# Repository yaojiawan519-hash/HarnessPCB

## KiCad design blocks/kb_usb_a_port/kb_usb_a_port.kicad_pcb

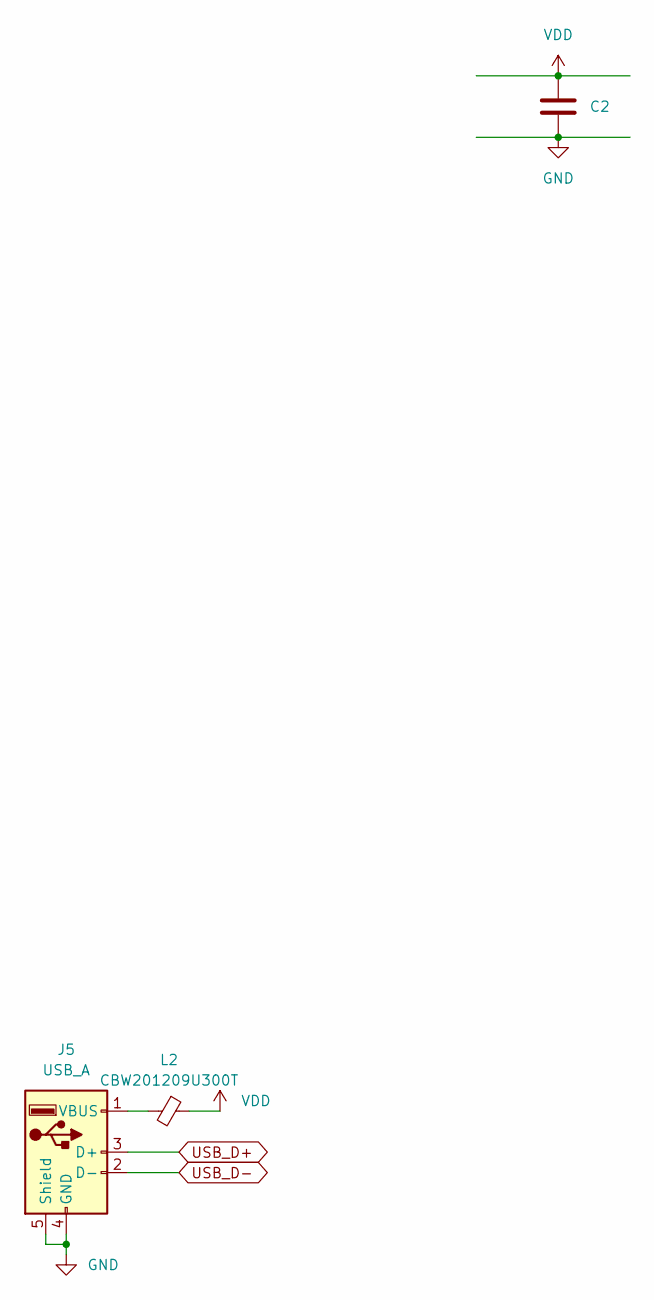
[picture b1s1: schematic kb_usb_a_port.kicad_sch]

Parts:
C2: 47uF/CL21A226MAYNNNE; C_0805_2012Metric
J5: USB_A; USB_A_CONNFLY_DS1095-WNR0
L2: CBW201209U300T; L_0805_2012Metric

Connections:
GND: C2.2, J5.4 (GND), J5.5 (Shield)
unnamed: J5.1 (VBUS), L2.2
USB_D+: J5.3 (D+)
USB_D-: J5.2 (D-)
VDD: C2.1, L2.1

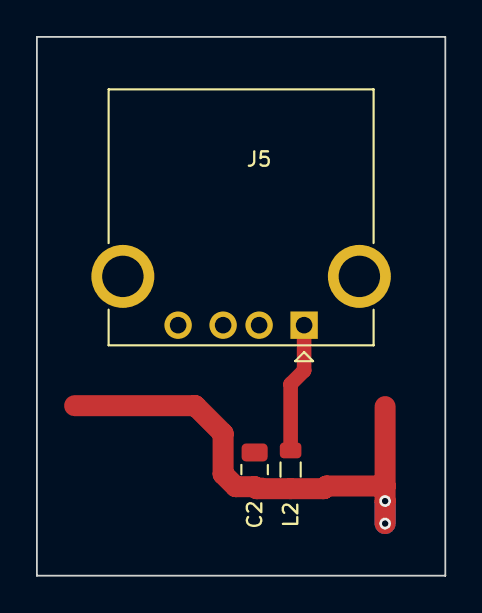
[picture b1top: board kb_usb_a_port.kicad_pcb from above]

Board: 2 copper layers, 22.7 x 29.9 mm, 3 parts (0 on the bottom side), 3 nets.

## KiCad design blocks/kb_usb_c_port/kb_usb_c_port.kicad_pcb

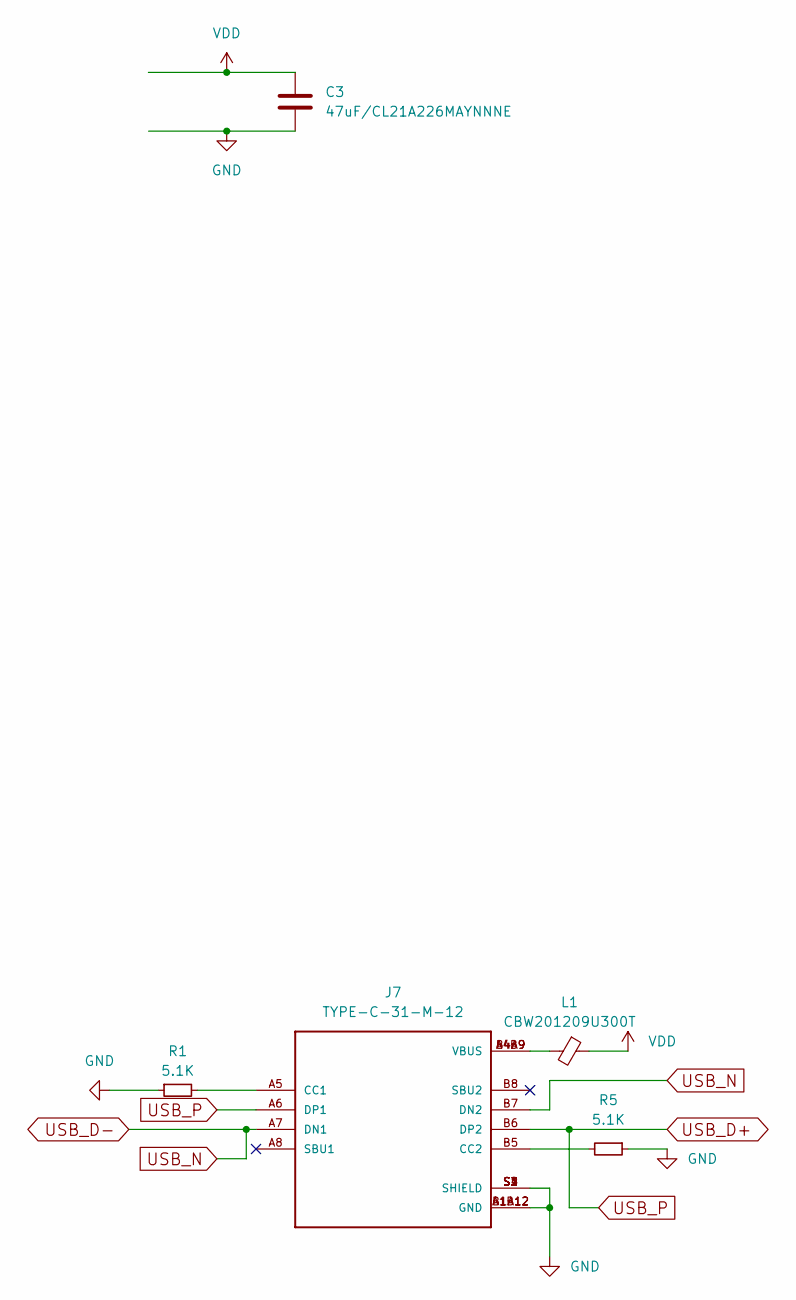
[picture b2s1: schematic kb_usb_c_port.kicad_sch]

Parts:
C3: 47uF/CL21A226MAYNNNE; C_0805_2012Metric
J7: TYPE-C-31-M-12; HRO_TYPE-C-31-M-12
L1: CBW201209U300T; L_0805_2012Metric
R1, R5: 5.1K; R_0805_2012Metric

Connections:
GND: C3.2, J7.A1B12 (GND), J7.B1A12 (GND), J7.S1 (SHIELD), J7.S2 (SHIELD), J7.S3 (SHIELD), J7.S4 (SHIELD), R1.1, R5.1
unnamed: J7.A5 (CC1), R1.2
unnamed: J7.B5 (CC2), R5.2
unnamed: J7.A4B9 (VBUS), J7.B4A9 (VBUS), L1.2
USB_D+: J7.A6 (DP1), J7.B6 (DP2)
USB_D-: J7.A7 (DN1), J7.B7 (DN2)
VDD: C3.1, L1.1

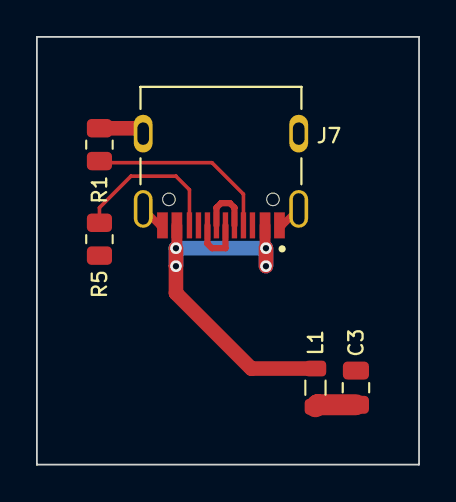
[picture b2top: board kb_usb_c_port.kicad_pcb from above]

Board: 2 copper layers, 21.2 x 23.8 mm, 5 parts (0 on the bottom side), 7 nets.

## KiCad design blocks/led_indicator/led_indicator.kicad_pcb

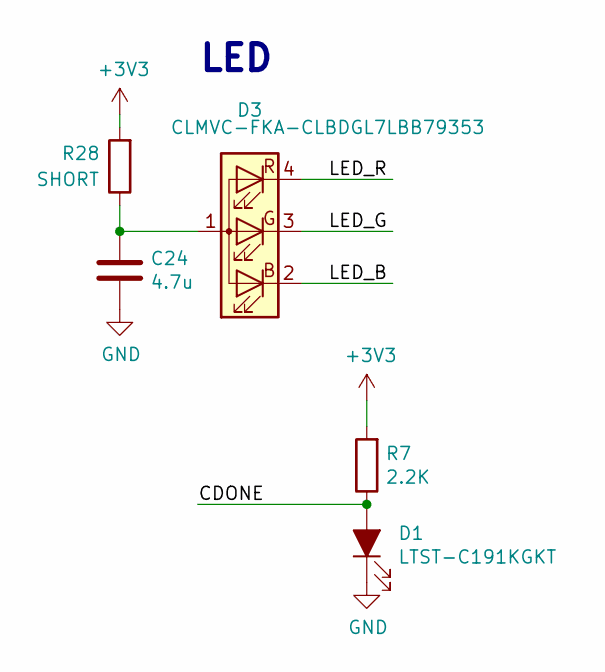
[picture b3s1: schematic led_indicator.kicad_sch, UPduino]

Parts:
C24: 4.7u; C_0603_1608Metric
D1: LTST-C191KGKT; LED_0603_1608Metric
D3: CLMVC-FKA-CLBDGL7LBB79353; LED_Cree-PLCC4_2x2mm_CW
R7: 2.2K; R_0603_1608Metric
R28: SHORT; ShortedJumper-2_P1.3mm_Bridged_Pad1.0x1.0mm

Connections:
+3V3: R7.2, R28.2
/CDONE: D1.2 (A), R7.1
/LED_B: D3.2 (RK)
/LED_G: D3.3 (GK)
/LED_R: D3.4 (BK)
GND: C24.2, D1.1 (K)
unnamed: C24.1, D3.1 (A), R28.1

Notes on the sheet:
LED

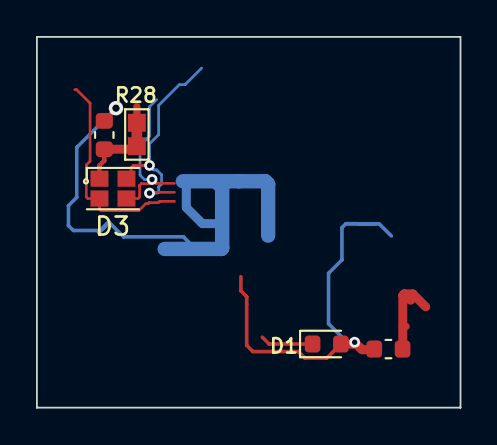
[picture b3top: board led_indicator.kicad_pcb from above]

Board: 4 copper layers, 23.5 x 20.6 mm, 5 parts (0 on the bottom side), 4 nets.

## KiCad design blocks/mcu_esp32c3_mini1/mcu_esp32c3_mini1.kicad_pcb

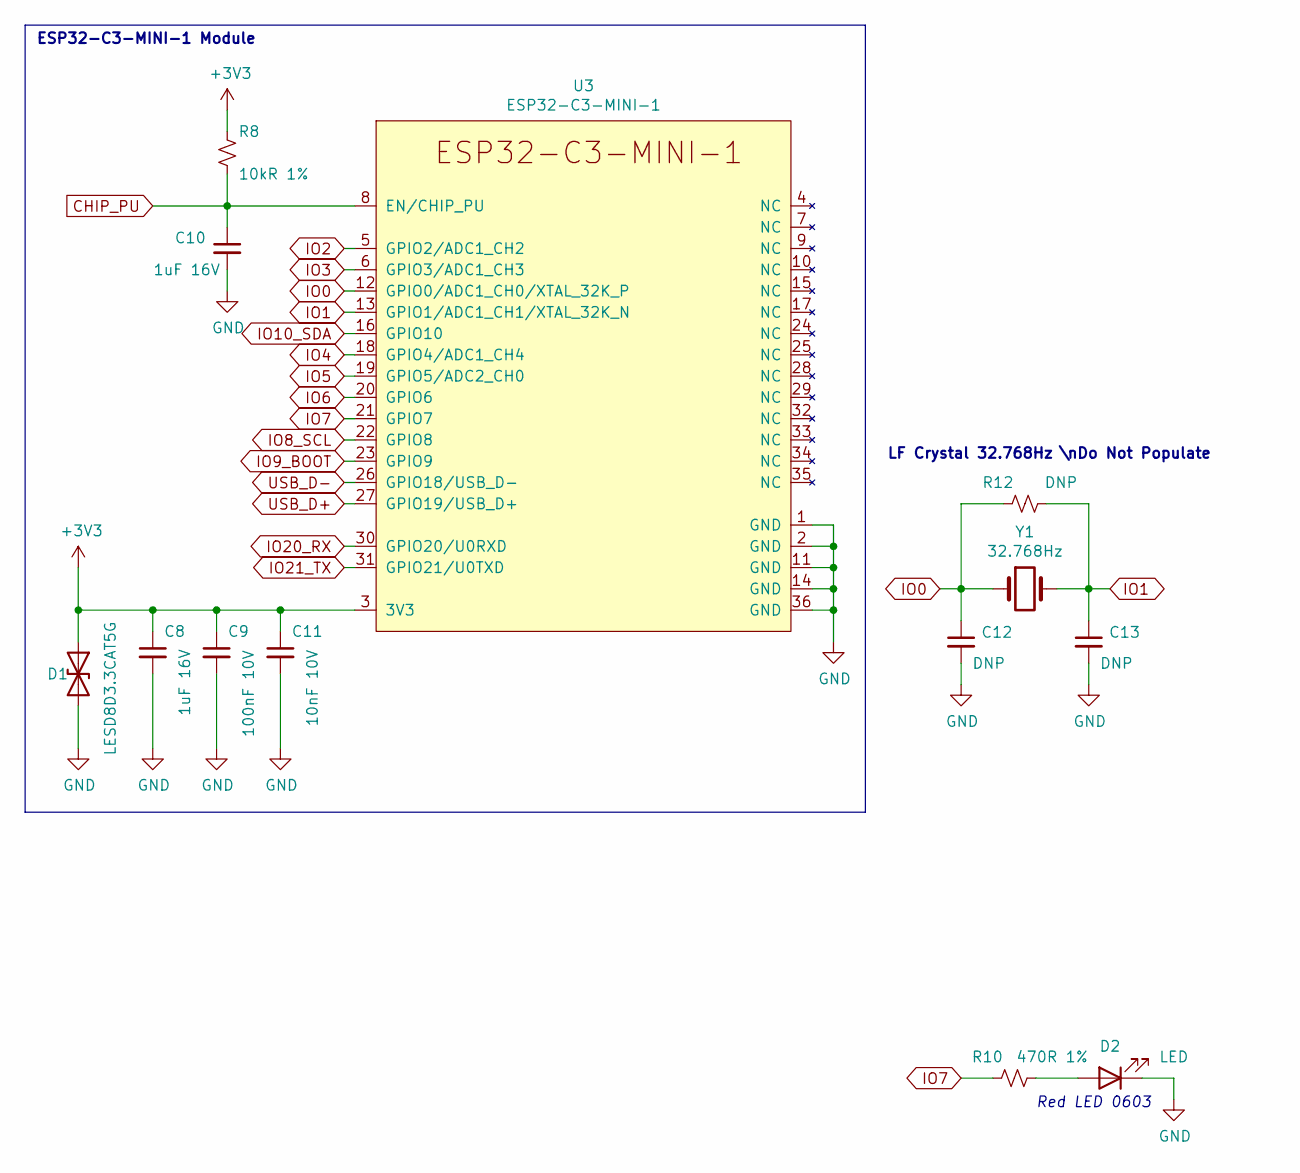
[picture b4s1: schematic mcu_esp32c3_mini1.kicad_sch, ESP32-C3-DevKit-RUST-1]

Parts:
C8, C10: 1uF 16V; C_0402_1005Metric; LCSC C52923
C9: 100nF 10V; C_0402_1005Metric; LCSC C1525
C11: 10nF 10V; C_0402_1005Metric; LCSC C15195
C12, C13: DNP; C_0402_1005Metric
D1: LESD8D3.3CAT5G; SOD-882; LCSC C172409
D2: LED; LED_0603_1608Metric; LCSC C2286
R8: 10kR 1%; R_0402_1005Metric; LCSC C25744
R10: 470R 1%; R_0402_1005Metric; LCSC C25117
R12: DNP; R_0402_1005Metric
U3: ESP32-C3-MINI-1; LCSC C2838502
Y1: 32.768Hz; Crystal_SMD_3215-2Pin_3.2x1.5mm

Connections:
+3V3: C8.1, C9.1, C11.1, D1.1 (A1), R8.1, U3.3 (3V3)
CHIP_PU: C10.1, R8.2, U3.8 (EN/CHIP_PU)
GND: C8.2, C9.2, C10.2, C11.2, C12.2, C13.2, D1.2 (A2), D2.1 (K), U3.1 (GND), U3.2 (GND), U3.11 (GND), U3.14 (GND), U3.36 (GND)
IO0: C12.1, R12.1, U3.12 (GPIO0/ADC1_CH0/XTAL_32K_P), Y1.1
IO1: C13.1, R12.2, U3.13 (GPIO1/ADC1_CH1/XTAL_32K_N), Y1.2
IO2: U3.5 (GPIO2/ADC1_CH2)
IO3: U3.6 (GPIO3/ADC1_CH3)
IO4: U3.18 (GPIO4/ADC1_CH4)
IO5: U3.19 (GPIO5/ADC2_CH0)
IO6: U3.20 (GPIO6)
IO7: R10.1, U3.21 (GPIO7)
IO8_SCL: U3.22 (GPIO8)
IO9_BOOT: U3.23 (GPIO9)
IO10_SDA: U3.16 (GPIO10)
IO20_RX: U3.30 (GPIO20/U0RXD)
IO21_TX: U3.31 (GPIO21/U0TXD)
unnamed: D2.2 (A), R10.2
USB_D+: U3.27 (GPIO19/USB_D+)
USB_D-: U3.26 (GPIO18/USB_D-)

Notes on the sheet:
LF Crystal 32.768Hz \nDo Not Populate
Red LED 0603
ESP32-C3-MINI-1 Module

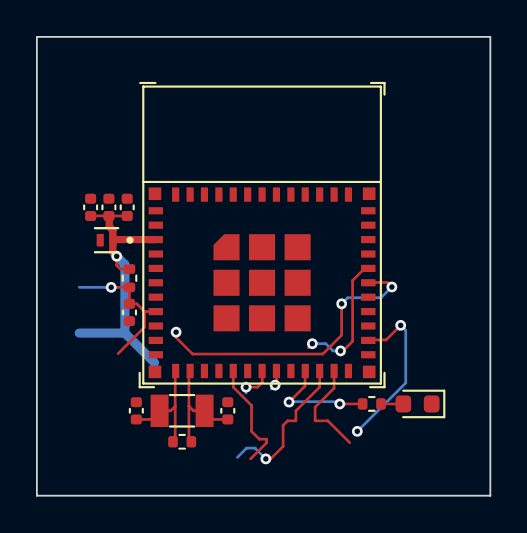
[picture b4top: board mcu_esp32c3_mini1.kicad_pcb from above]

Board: 2 copper layers, 25.2 x 25.5 mm, 13 parts (0 on the bottom side), 7 nets.

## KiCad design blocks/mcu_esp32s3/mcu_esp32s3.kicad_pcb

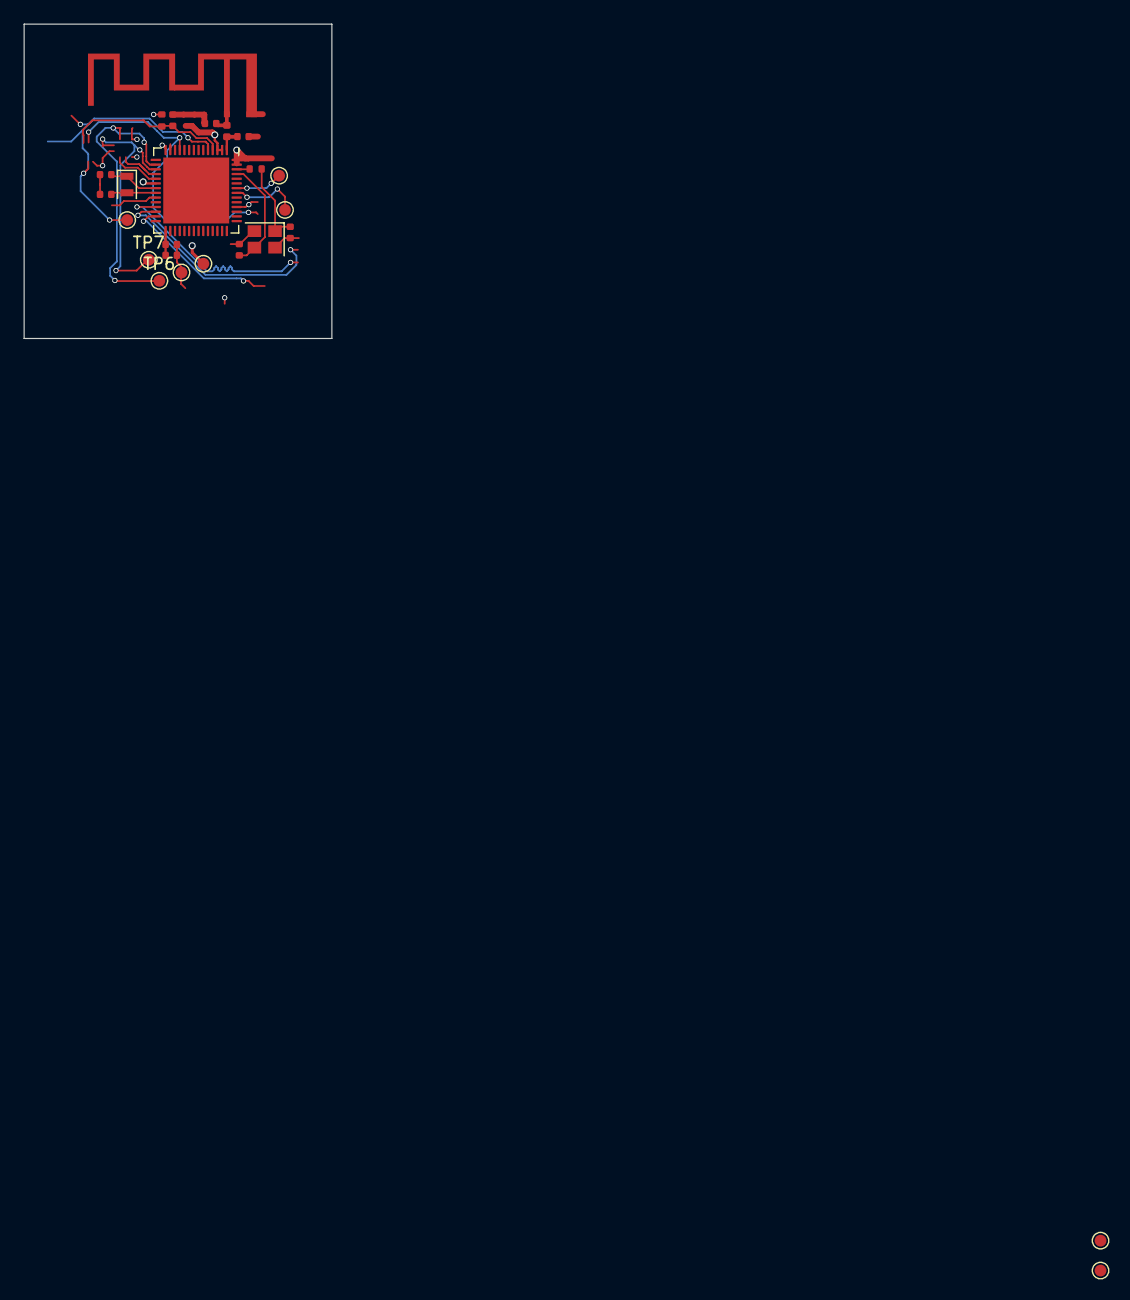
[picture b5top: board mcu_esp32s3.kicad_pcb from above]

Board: 4 copper layers, 26.1 x 26.7 mm, 25 parts (0 on the bottom side), 16 nets.

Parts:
AE1: Antenna_Chip; SWRA117D
C2, C15: 1uF; C_0402_1005Metric
C7, C9: TBD; C_0402_1005Metric
C13: 100nF; C_0402_1005Metric
C16, C19: 22pF; C_0402_1005Metric
C17, C18: 18pF; C_0402_1005Metric
L1: TBD; L_0402_1005Metric
R1: 10K; R_0402_1005Metric
R12: TBD; R_0402_1005Metric
TP1: TX; TestPoint_Pad_D1.0mm
TP2: RX; TestPoint_Pad_D1.0mm
TP3: BOOT; TestPoint_Pad_D1.0mm
TP4, TP4#2: 3V3; TestPoint_Pad_D1.0mm
TP5, TP5#2: GND; TestPoint_Pad_D1.0mm
TP6: SCL; TestPoint_Pad_D1.0mm
TP7: SDA; TestPoint_Pad_D1.0mm
U4: ESP32-S3; QFN-56-1EP_7x7mm_P0.4mm_EP5.6x5.6mm
Y1: 32.768KHz; Crystal_SMD_2012-2Pin_2.0x1.2mm
Y2: 40MHz; Crystal_SMD_2520-4Pin_2.5x2.0mm

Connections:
+3V3: R1.2, TP4.1, TP4#2.1, U4.2 (VDD3P3), U4.3 (VDD3P3), U4.20 (VDD3P3_RTC), U4.46 (VDD3P3_CPU), U4.55 (VDDA), U4.56 (VDDA)
/32K_N: C18.1, U4.22 (GPIO16/ADC2_CH5/XTAL_32K_N), Y1.2
/32K_P: C17.1, U4.21 (GPIO15/ADC2_CH4/XTAL_32K_P), Y1.1
/40M_N: C19.1, U4.53 (XTAL_N), Y2.3
/40M_P: C16.1, R12.2, Y2.1
BTN3: TP3.1, U4.5 (GPIO0/BOOT)
EN: C2.1, R1.1, U4.4 (CHIP_PU/RESET)
GND: AE1.2 (PCB_Trace), C2.2, C7.2, C9.2, C13.2, C15.2, C16.2, C17.2, C18.2, C19.2, TP5.1, TP5#2.1, U4.57 (GND), Y2.2, Y2.4
unnamed: AE1.1 (FEED), C7.1, L1.1
unnamed: C9.1, L1.2, U4.1 (LNA_IN/RF)
unnamed: TP2.1, U4.50 (U0RXD/PROG/GPIO44)
unnamed: TP1.1, U4.49 (U0TXD/PROG/GPIO43)
unnamed: R12.1, U4.54 (XTAL_P)
SCL: TP6.1, U4.16 (GPIO11/ADC2_CH0)
SDA: TP7.1, U4.17 (GPIO12/ADC2_CH1)
VDD: C13.1, C15.1, U4.29 (VDD_SPI)

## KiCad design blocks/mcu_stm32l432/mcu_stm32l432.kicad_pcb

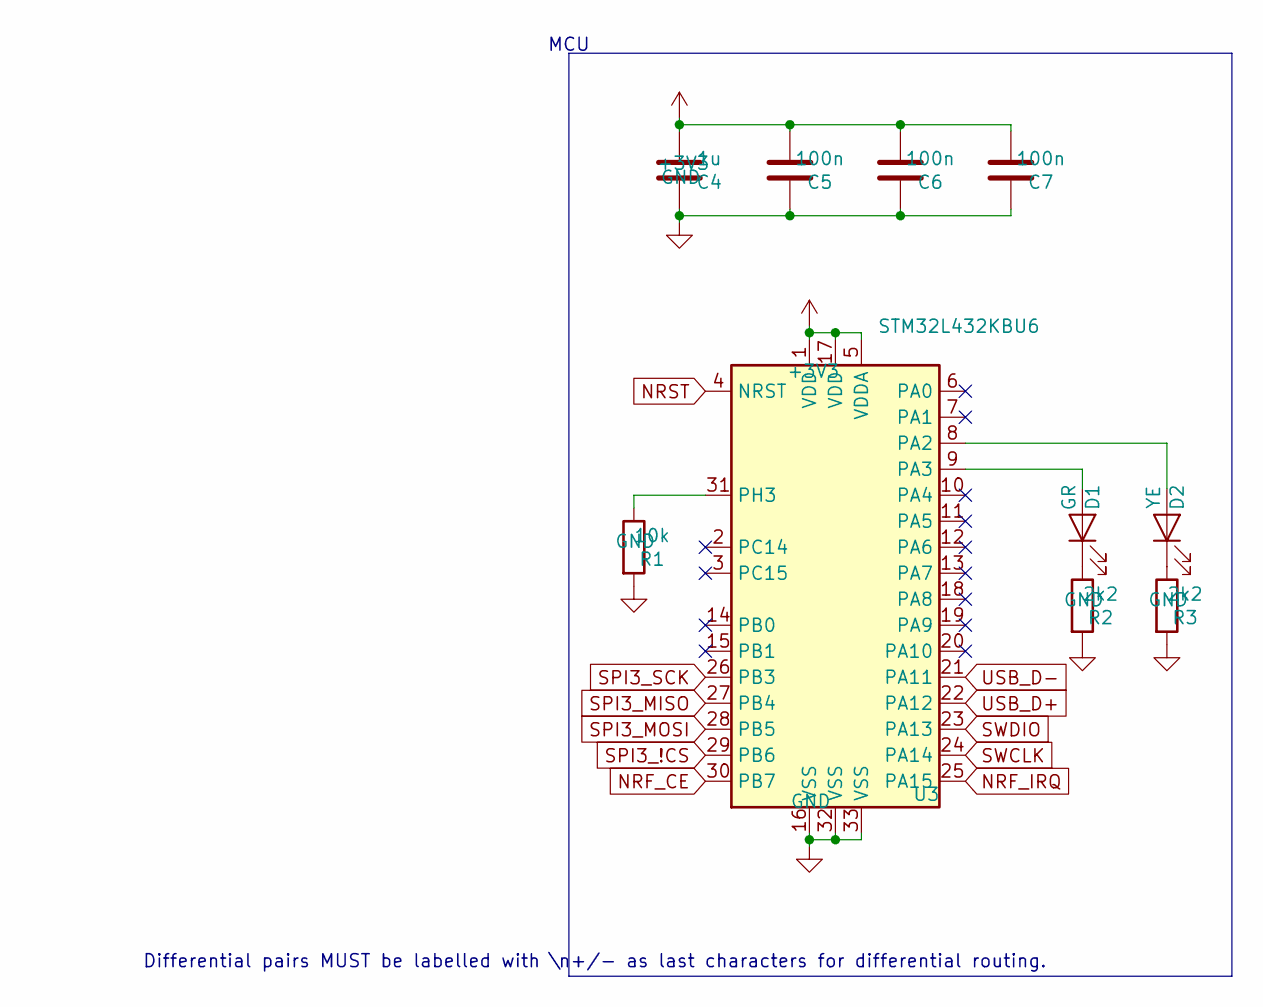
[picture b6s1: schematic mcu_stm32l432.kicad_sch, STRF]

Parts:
C4: 1u; C_0402_1005Metric
C5, C6, C7: 100n; C_0402_1005Metric
D1: GR; LED_0603_1608Metric
D2: YE; LED_0603_1608Metric
R1: 10k; R_0402_1005Metric
R2, R3: 2k2; R_0603_1608Metric
U3: STM32L432KBU6; QFN-32-1EP_5x5mm_P0.5mm_EP3.45x3.45mm

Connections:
+3V3: C4.1, C5.1, C6.1, C7.1, U3.1 (VDD), U3.5 (VDDA), U3.17 (VDD)
GND: C4.2, C5.2, C6.2, C7.2, R1.2, R2.2, R3.2, U3.16 (VSS), U3.32 (VSS), U3.33 (VSS)
NRF_CE: U3.30 (PB7)
NRF_IRQ: U3.25 (PA15)
NRST: U3.4 (NRST)
unnamed: D1.1 (K), R2.1
unnamed: D1.2 (A), U3.9 (PA3)
unnamed: D2.1 (K), R3.1
unnamed: D2.2 (A), U3.8 (PA2)
unnamed: R1.1, U3.31 (PH3)
SPI3_!CS: U3.29 (PB6)
SPI3_MISO: U3.27 (PB4)
SPI3_MOSI: U3.28 (PB5)
SPI3_SCK: U3.26 (PB3)
SWCLK: U3.24 (PA14)
SWDIO: U3.23 (PA13)
USB_D+: U3.22 (PA12)
USB_D-: U3.21 (PA11)

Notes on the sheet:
Differential pairs MUST be labelled with \n+/- as last characters for differential routing.
MCU

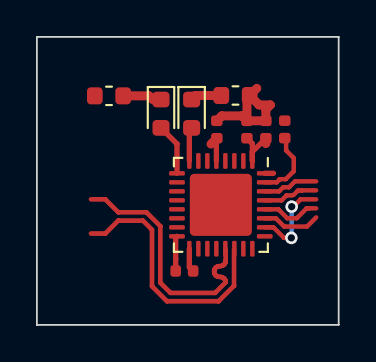
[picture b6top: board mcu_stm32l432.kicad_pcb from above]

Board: 2 copper layers, 16.8 x 16.0 mm, 10 parts (0 on the bottom side), 7 nets.
